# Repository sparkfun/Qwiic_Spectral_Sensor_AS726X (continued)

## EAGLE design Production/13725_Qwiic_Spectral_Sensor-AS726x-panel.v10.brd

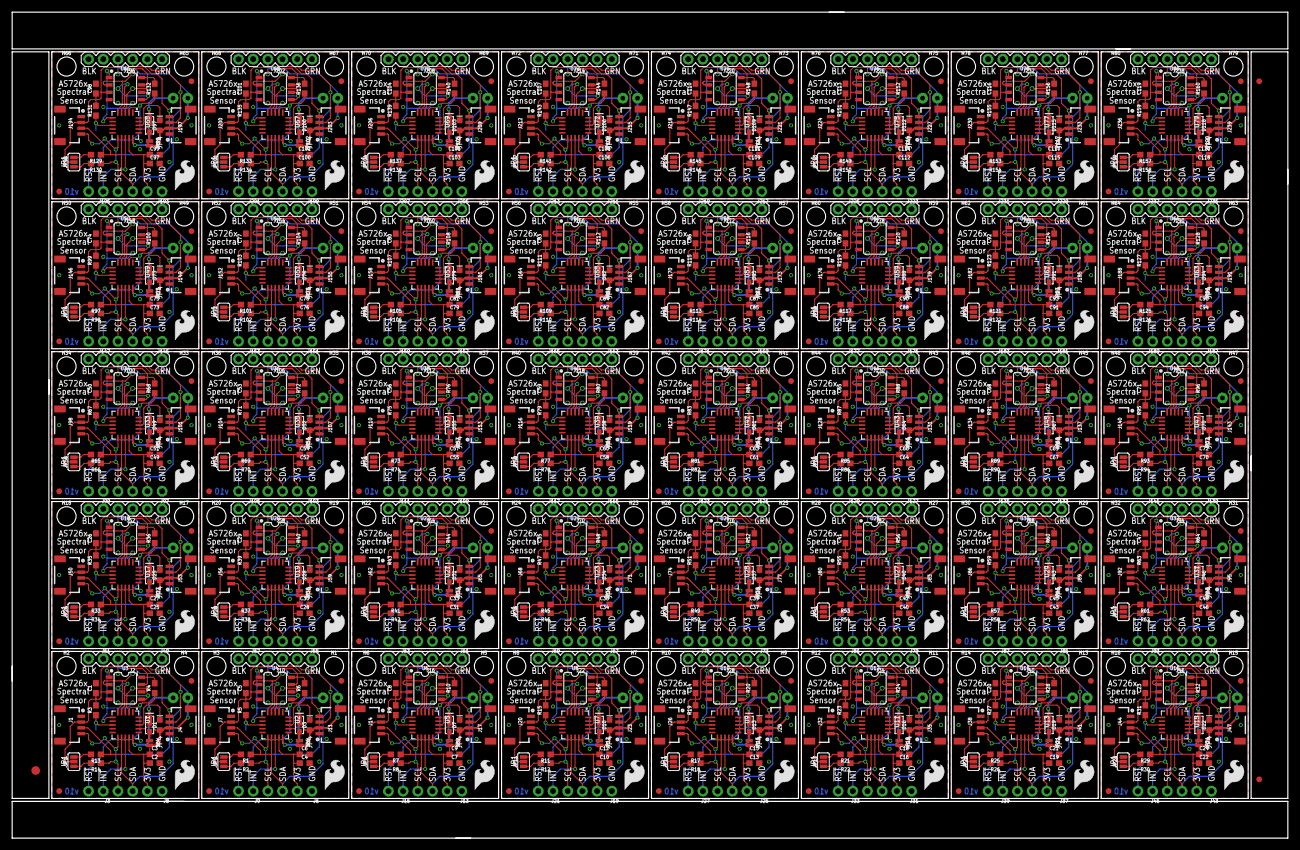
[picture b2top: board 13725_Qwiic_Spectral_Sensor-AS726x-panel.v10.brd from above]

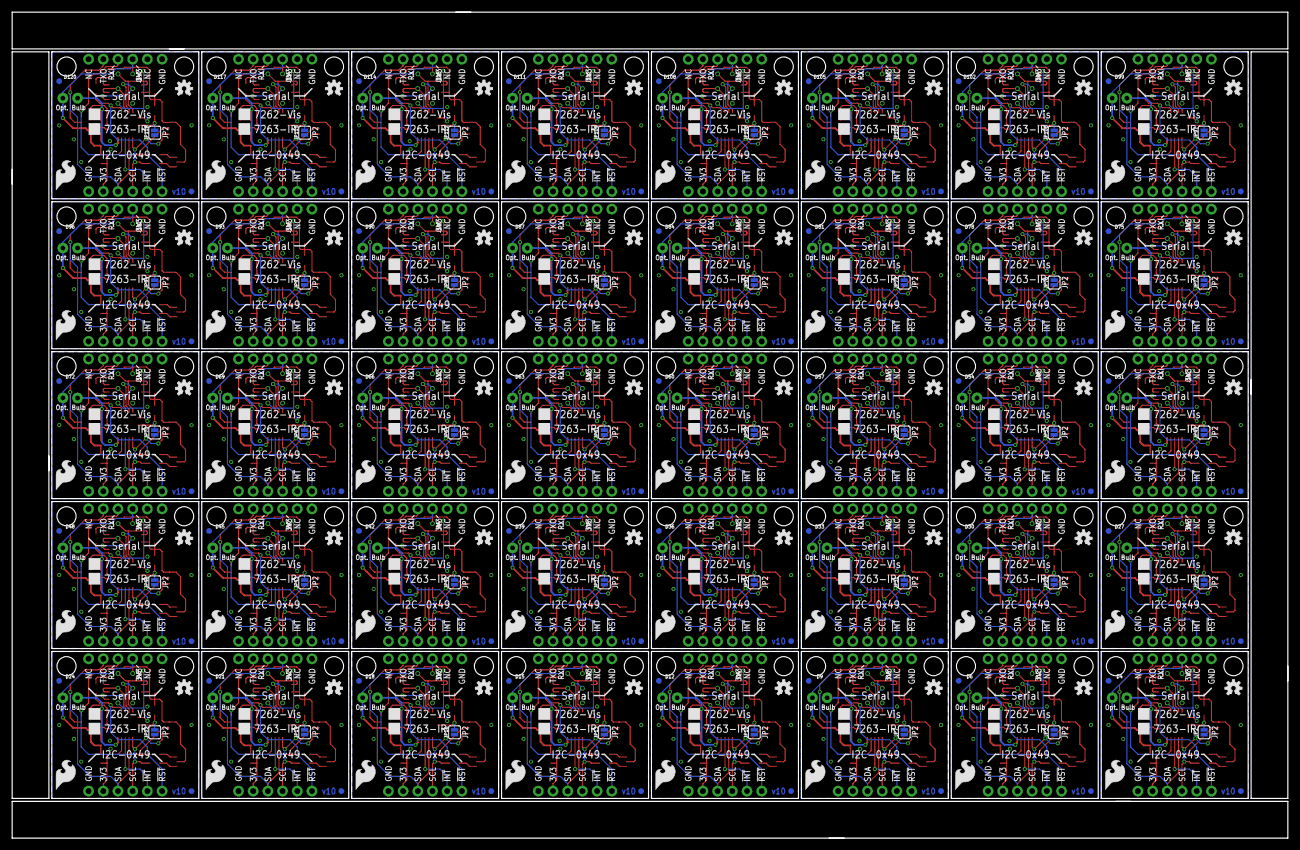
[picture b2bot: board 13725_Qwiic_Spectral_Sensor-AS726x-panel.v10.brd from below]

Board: 2 copper layers, 220.5 x 142.7 mm, 1203 parts (280 on the bottom side), 640 nets.

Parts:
C1, C2, C4, C5, C7, C8, C10, C11, C13, C14, C16, C17, C19, C20, C22, C23, C25, C26, C28, C29, C31, C32, C34, C35, C37, C38, C40, C41, C43, C44, C46, C47, C49, C50, C52, C53, C55, C56, C58, C59, C61, C62, C64, C65, C67, C68, C70, C71, C73, C74, C76, C77, C79, C80, C82, C83, C85, C86, C88, C89, C91, C92, C94, C95, C97, C98, C100, C101, C103, C104, C106, C107, C109, C110, C112, C113, C115, C116, C118, C119: 1.0uF; 0603
C3, C6, C9, C12, C15, C18, C21, C24, C27, C30, C33, C36, C39, C42, C45, C48, C51, C54, C57, C60, C63, C66, C69, C72, C75, C78, C81, C84, C87, C90, C93, C96, C99, C102, C105, C108, C111, C114, C117, C120: 10uF; 0603
D1, D3, D7, D10, D13, D16, D19, D22, D25, D28, D31, D34, D37, D40, D43, D46, D49, D52, D55, D58, D61, D64, D67, D70, D73, D76, D79, D82, D85, D88, D91, D94, D97, D100, D103, D106, D109, D112, D115, D118: BLUE; LED-0603
D2, D5, D8, D11, D14, D17, D20, D23, D26, D29, D32, D35, D38, D41, D44, D47, D50, D53, D56, D59, D62, D65, D68, D71, D74, D77, D80, D83, D86, D89, D92, D95, D98, D101, D104, D107, D110, D113, D116, D119: White, 60mA; SUPER_BRIGHT_SMD_LED_3014
D4, D6, D9, D12, D15, D18, D21, D24, D27, D30, D33, D36, D39, D42, D45, D48, D51, D54, D57, D60, D63, D66, D69, D72, D75, D78, D81, D84, D87, D90, D93, D96, D99, D102, D105, D108, D111, D114, D117, D120: Incandescent; LED_5MM_NOSILK
E$1: FIDUCIAL-1.5X3
E$7, E$8: FIDUCIAL-1X2
FD1, FD2, FD3, FD4, FD5, FD6, FD7, FD8, FD9, FD10, FD11, FD12, FD13, FD14, FD15, FD16, FD17, FD18, FD19, FD20, FD21, FD22, FD23, FD24, FD25, FD26, FD27, FD28, FD29, FD30, FD31, FD32, FD33, FD34, FD35, FD36, FD37, FD38, FD39, FD40, FD41, FD42, FD43, FD44, FD45, FD46, FD47, FD48, FD49, FD50, FD51, FD52, FD53, FD54, FD55, FD56, FD57, FD58, FD59, FD60, FD61, FD62, FD63, FD64, FD65, FD66, FD67, FD68, FD69, FD70, FD71, FD72, FD73, FD74, FD75, FD76, FD77, FD78, FD79, FD80, FD81, FD82, FD83, FD84, FD85, FD86, FD87, FD88, FD89, FD90, FD91, FD92, FD93, FD94, FD95, FD96, FD97, FD98, FD99, FD100, FD101, FD102, FD103, FD104, FD105, FD106, FD107, FD108, FD109, FD110, FD111, FD112, FD113, FD114, FD115, FD116, FD117, FD118, FD119, FD120, FD121, FD122, FD123, FD124, FD125, FD126, FD127, FD128, FD129, FD130, FD131, FD132, FD133, FD134, FD135, FD136, FD137, FD138, FD139, FD140, FD141, FD142, FD143, FD144, FD145, FD146, FD147, FD148, FD149, FD150, FD151, FD152, FD153, FD154, FD155, FD156, FD157, FD158, FD159, FD160: FIDUCIAL1X2; FIDUCIAL-1X2
H1, H2, H3, H4, H5, H6, H7, H8, H9, H10, H11, H12, H13, H14, H15, H16, H17, H18, H19, H20, H21, H22, H23, H24, H25, H26, H27, H28, H29, H30, H31, H32, H33, H34, H35, H36, H37, H38, H39, H40, H41, H42, H43, H44, H45, H46, H47, H48, H49, H50, H51, H52, H53, H54, H55, H56, H57, H58, H59, H60, H61, H62, H63, H64, H65, H66, H67, H68, H69, H70, H71, H72, H73, H74, H75, H76, H77, H78, H79, H80: STAND-OFF
J1, J4, J7, J11, J14, J17, J20, J23, J26, J29, J32, J35, J38, J41, J44, J47, J50, J53, J56, J59, J62, J65, J68, J71, J74, J77, J80, J83, J86, J89, J92, J95, J98, J101, J104, J107, J110, J113, J116, J119, J122, J125, J128, J131, J134, J137, J140, J143, J146, J149, J152, J155, J158, J161, J164, J167, J170, J173, J176, J179, J182, J185, J188, J191, J194, J197, J200, J203, J206, J209, J212, J215, J218, J221, J224, J227, J230, J233, J236, J239: Qwiic Right Angle; 1X04_1MM_RA
J2, J10, J16, J22, J28, J34, J40, J46, J52, J58, J64, J70, J76, J82, J88, J94, J100, J106, J112, J118, J124, J130, J136, J142, J148, J154, J160, J166, J172, J178, J184, J190, J196, J202, J208, J214, J220, J226, J232, J238: Serial Interface; FTDI_BASIC
J3, J9, J15, J21, J27, J33, J39, J45, J51, J57, J63, J69, J75, J81, J87, J93, J99, J105, J111, J117, J123, J129, J135, J141, J147, J153, J159, J165, J171, J177, J183, J189, J195, J201, J207, J213, J219, J225, J231, J237: 1X02_NO_SILK
J5, J12, J18, J24, J30, J36, J42, J48, J54, J60, J66, J72, J78, J84, J90, J96, J102, J108, J114, J120, J126, J132, J138, J144, J150, J156, J162, J168, J174, J180, J186, J192, J198, J204, J210, J216, J222, J228, J234, J240: Flash Programming; 2X3_TEST_POINTS
J6, J8, J13, J19, J25, J31, J37, J43, J49, J55, J61, J67, J73, J79, J85, J91, J97, J103, J109, J115, J121, J127, J133, J139, J145, J151, J157, J163, J169, J175, J181, J187, J193, J199, J205, J211, J217, J223, J229, J235: 1X04_NO_SILK
JP1, JP5, JP8, JP11, JP14, JP17, JP20, JP23, JP26, JP29, JP32, JP35, JP38, JP41, JP44, JP47, JP50, JP53, JP56, JP59, JP62, JP65, JP68, JP71, JP74, JP77, JP80, JP83, JP86, JP89, JP92, JP95, JP98, JP101, JP104, JP107, JP110, JP113, JP116, JP119: SMT-JUMPER_3_2-NC_PASTE_SILK
JP2, JP3, JP7, JP10, JP13, JP16, JP19, JP22, JP25, JP28, JP31, JP34, JP37, JP40, JP43, JP46, JP49, JP52, JP55, JP58, JP61, JP64, JP67, JP70, JP73, JP76, JP79, JP82, JP85, JP88, JP91, JP94, JP97, JP100, JP103, JP106, JP109, JP112, JP115, JP118: SMT-JUMPER_2_NO_SILK
JP4, JP6, JP9, JP12, JP15, JP18, JP21, JP24, JP27, JP30, JP33, JP36, JP39, JP42, JP45, JP48, JP51, JP54, JP57, JP60, JP63, JP66, JP69, JP72, JP75, JP78, JP81, JP84, JP87, JP90, JP93, JP96, JP99, JP102, JP105, JP108, JP111, JP114, JP117, JP120: SMT-JUMPER_2_NC_PASTE_NO-SILK
LOGO1, LOGO2, LOGO5, LOGO6, LOGO8, LOGO9, LOGO11, LOGO12, LOGO14, LOGO15, LOGO17, LOGO18, LOGO20, LOGO21, LOGO23, LOGO24, LOGO26, LOGO27, LOGO29, LOGO30, LOGO32, LOGO33, LOGO35, LOGO36, LOGO38, LOGO39, LOGO41, LOGO42, LOGO44, LOGO45, LOGO47, LOGO48, LOGO50, LOGO51, LOGO53, LOGO54, LOGO56, LOGO57, LOGO59, LOGO60, LOGO62, LOGO63, LOGO65, LOGO66, LOGO68, LOGO69, LOGO71, LOGO72, LOGO74, LOGO75, LOGO77, LOGO78, LOGO80, LOGO81, LOGO83, LOGO84, LOGO86, LOGO87, LOGO89, LOGO90, LOGO92, LOGO93, LOGO95, LOGO96, LOGO98, LOGO99, LOGO101, LOGO102, LOGO104, LOGO105, LOGO107, LOGO108, LOGO110, LOGO111, LOGO113, LOGO114, LOGO116, LOGO117, LOGO119, LOGO120: SFE_LOGO_FLAME.2_INCH; SFE_LOGO_FLAME_.2
LOGO3, LOGO4, LOGO7, LOGO10, LOGO13, LOGO16, LOGO19, LOGO22, LOGO25, LOGO28, LOGO31, LOGO34, LOGO37, LOGO40, LOGO43, LOGO46, LOGO49, LOGO52, LOGO55, LOGO58, LOGO61, LOGO64, LOGO67, LOGO70, LOGO73, LOGO76, LOGO79, LOGO82, LOGO85, LOGO88, LOGO91, LOGO94, LOGO97, LOGO100, LOGO103, LOGO106, LOGO109, LOGO112, LOGO115, LOGO118: OSHW-LOGOS; OSHW-LOGO-S
R1, R2, R7, R8, R11, R12, R13, R14, R17, R18, R21, R22, R25, R26, R29, R30, R33, R34, R37, R38, R41, R42, R45, R46, R49, R50, R53, R54, R57, R58, R61, R62, R65, R66, R69, R70, R73, R74, R77, R78, R81, R82, R85, R86, R89, R90, R93, R94, R97, R98, R101, R102, R105, R106, R109, R110, R113, R114, R117, R118, R121, R122, R125, R126, R129, R130, R133, R134, R137, R138, R141, R142, R145, R146, R149, R150, R153, R154, R157, R158: 4.7k; 0603
R3, R4, R5, R6, R9, R10, R15, R16, R19, R20, R23, R24, R27, R28, R31, R32, R35, R36, R39, R40, R43, R44, R47, R48, R51, R52, R55, R56, R59, R60, R63, R64, R67, R68, R71, R72, R75, R76, R79, R80, R83, R84, R87, R88, R91, R92, R95, R96, R99, R100, R103, R104, R107, R108, R111, R112, R115, R116, R119, R120, R123, R124, R127, R128, R131, R132, R135, R136, R139, R140, R143, R144, R147, R148, R151, R152, R155, R156, R159, R160: 10k; 0603
U1, U2, U5, U7, U9, U11, U13, U15, U17, U19, U21, U23, U25, U27, U29, U31, U33, U35, U37, U39, U41, U43, U45, U47, U49, U51, U53, U55, U57, U59, U61, U63, U65, U67, U69, U71, U73, U75, U77, U79: IR; LGA20
U3, U4, U6, U8, U10, U12, U14, U16, U18, U20, U22, U24, U26, U28, U30, U32, U34, U36, U38, U40, U42, U44, U46, U48, U50, U52, U54, U56, U58, U60, U62, U64, U66, U68, U70, U72, U74, U76, U78, U80: 4MB Flash; SO08

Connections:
3.3V: C1.1, C2.1, C3.1, D1.A, D4.A, J1.2, J2.VCC, J4.2, J5.2, J8.2, JP1.2, JP4.2, R3.2, R4.2, U1.14, U1.17, U3.3, U3.7, U3.8
3.3V1: C4.1, C5.1, C6.1, D3.A, D6.A, J6.2, J7.2, J10.VCC, J11.2, J12.2, JP5.2, JP6.2, R5.2, R6.2, U2.14, U2.17, U4.3, U4.7, U4.8
3.3V2: C7.1, C8.1, C9.1, D7.A, D9.A, J13.2, J14.2, J16.VCC, J17.2, J18.2, JP8.2, JP9.2, R9.2, R10.2, U5.14, U5.17, U6.3, U6.7, U6.8
3.3V3: C10.1, C11.1, C12.1, D10.A, D12.A, J19.2, J20.2, J22.VCC, J23.2, J24.2, JP11.2, JP12.2, R15.2, R16.2, U7.14, U7.17, U8.3, U8.7, U8.8
3.3V4: C13.1, C14.1, C15.1, D13.A, D15.A, J25.2, J26.2, J28.VCC, J29.2, J30.2, JP14.2, JP15.2, R19.2, R20.2, U9.14, U9.17, U10.3, U10.7, U10.8
3.3V5: C16.1, C17.1, C18.1, D16.A, D18.A, J31.2, J32.2, J34.VCC, J35.2, J36.2, JP17.2, JP18.2, R23.2, R24.2, U11.14, U11.17, U12.3, U12.7, U12.8
3.3V6: C19.1, C20.1, C21.1, D19.A, D21.A, J37.2, J38.2, J40.VCC, J41.2, J42.2, JP20.2, JP21.2, R27.2, R28.2, U13.14, U13.17, U14.3, U14.7, U14.8
3.3V7: C22.1, C23.1, C24.1, D22.A, D24.A, J43.2, J44.2, J46.VCC, J47.2, J48.2, JP23.2, JP24.2, R31.2, R32.2, U15.14, U15.17, U16.3, U16.7, U16.8
3.3V8: C25.1, C26.1, C27.1, D25.A, D27.A, J49.2, J50.2, J52.VCC, J53.2, J54.2, JP26.2, JP27.2, R35.2, R36.2, U17.14, U17.17, U18.3, U18.7, U18.8
3.3V9: C28.1, C29.1, C30.1, D28.A, D30.A, J55.2, J56.2, J58.VCC, J59.2, J60.2, JP29.2, JP30.2, R39.2, R40.2, U19.14, U19.17, U20.3, U20.7, U20.8
3.3V10: C31.1, C32.1, C33.1, D31.A, D33.A, J61.2, J62.2, J64.VCC, J65.2, J66.2, JP32.2, JP33.2, R43.2, R44.2, U21.14, U21.17, U22.3, U22.7, U22.8
3.3V11: C34.1, C35.1, C36.1, D34.A, D36.A, J67.2, J68.2, J70.VCC, J71.2, J72.2, JP35.2, JP36.2, R47.2, R48.2, U23.14, U23.17, U24.3, U24.7, U24.8
3.3V12: C37.1, C38.1, C39.1, D37.A, D39.A, J73.2, J74.2, J76.VCC, J77.2, J78.2, JP38.2, JP39.2, R51.2, R52.2, U25.14, U25.17, U26.3, U26.7, U26.8
3.3V13: C40.1, C41.1, C42.1, D40.A, D42.A, J79.2, J80.2, J82.VCC, J83.2, J84.2, JP41.2, JP42.2, R55.2, R56.2, U27.14, U27.17, U28.3, U28.7, U28.8
3.3V14: C43.1, C44.1, C45.1, D43.A, D45.A, J85.2, J86.2, J88.VCC, J89.2, J90.2, JP44.2, JP45.2, R59.2, R60.2, U29.14, U29.17, U30.3, U30.7, U30.8
3.3V15: C46.1, C47.1, C48.1, D46.A, D48.A, J91.2, J92.2, J94.VCC, J95.2, J96.2, JP47.2, JP48.2, R63.2, R64.2, U31.14, U31.17, U32.3, U32.7, U32.8
3.3V16: C49.1, C50.1, C51.1, D49.A, D51.A, J97.2, J98.2, J100.VCC, J101.2, J102.2, JP50.2, JP51.2, R67.2, R68.2, U33.14, U33.17, U34.3, U34.7, U34.8
3.3V17: C52.1, C53.1, C54.1, D52.A, D54.A, J103.2, J104.2, J106.VCC, J107.2, J108.2, JP53.2, JP54.2, R71.2, R72.2, U35.14, U35.17, U36.3, U36.7, U36.8
3.3V18: C55.1, C56.1, C57.1, D55.A, D57.A, J109.2, J110.2, J112.VCC, J113.2, J114.2, JP56.2, JP57.2, R75.2, R76.2, U37.14, U37.17, U38.3, U38.7, U38.8
3.3V19: C58.1, C59.1, C60.1, D58.A, D60.A, J115.2, J116.2, J118.VCC, J119.2, J120.2, JP59.2, JP60.2, R79.2, R80.2, U39.14, U39.17, U40.3, U40.7, U40.8
3.3V20: C61.1, C62.1, C63.1, D61.A, D63.A, J121.2, J122.2, J124.VCC, J125.2, J126.2, JP62.2, JP63.2, R83.2, R84.2, U41.14, U41.17, U42.3, U42.7, U42.8
3.3V21: C64.1, C65.1, C66.1, D64.A, D66.A, J127.2, J128.2, J130.VCC, J131.2, J132.2, JP65.2, JP66.2, R87.2, R88.2, U43.14, U43.17, U44.3, U44.7, U44.8
3.3V22: C67.1, C68.1, C69.1, D67.A, D69.A, J133.2, J134.2, J136.VCC, J137.2, J138.2, JP68.2, JP69.2, R91.2, R92.2, U45.14, U45.17, U46.3, U46.7, U46.8
3.3V23: C70.1, C71.1, C72.1, D70.A, D72.A, J139.2, J140.2, J142.VCC, J143.2, J144.2, JP71.2, JP72.2, R95.2, R96.2, U47.14, U47.17, U48.3, U48.7, U48.8
3.3V24: C73.1, C74.1, C75.1, D73.A, D75.A, J145.2, J146.2, J148.VCC, J149.2, J150.2, JP74.2, JP75.2, R99.2, R100.2, U49.14, U49.17, U50.3, U50.7, U50.8
3.3V25: C76.1, C77.1, C78.1, D76.A, D78.A, J151.2, J152.2, J154.VCC, J155.2, J156.2, JP77.2, JP78.2, R103.2, R104.2, U51.14, U51.17, U52.3, U52.7, U52.8
3.3V26: C79.1, C80.1, C81.1, D79.A, D81.A, J157.2, J158.2, J160.VCC, J161.2, J162.2, JP80.2, JP81.2, R107.2, R108.2, U53.14, U53.17, U54.3, U54.7, U54.8
3.3V27: C82.1, C83.1, C84.1, D82.A, D84.A, J163.2, J164.2, J166.VCC, J167.2, J168.2, JP83.2, JP84.2, R111.2, R112.2, U55.14, U55.17, U56.3, U56.7, U56.8
3.3V28: C85.1, C86.1, C87.1, D85.A, D87.A, J169.2, J170.2, J172.VCC, J173.2, J174.2, JP86.2, JP87.2, R115.2, R116.2, U57.14, U57.17, U58.3, U58.7, U58.8
3.3V29: C88.1, C89.1, C90.1, D88.A, D90.A, J175.2, J176.2, J178.VCC, J179.2, J180.2, JP89.2, JP90.2, R119.2, R120.2, U59.14, U59.17, U60.3, U60.7, U60.8
3.3V30: C91.1, C92.1, C93.1, D91.A, D93.A, J181.2, J182.2, J184.VCC, J185.2, J186.2, JP92.2, JP93.2, R123.2, R124.2, U61.14, U61.17, U62.3, U62.7, U62.8
3.3V31: C94.1, C95.1, C96.1, D94.A, D96.A, J187.2, J188.2, J190.VCC, J191.2, J192.2, JP95.2, JP96.2, R127.2, R128.2, U63.14, U63.17, U64.3, U64.7, U64.8
3.3V32: C97.1, C98.1, C99.1, D97.A, D99.A, J193.2, J194.2, J196.VCC, J197.2, J198.2, JP98.2, JP99.2, R131.2, R132.2, U65.14, U65.17, U66.3, U66.7, U66.8
3.3V33: C100.1, C101.1, C102.1, D100.A, D102.A, J199.2, J200.2, J202.VCC, J203.2, J204.2, JP101.2, JP102.2, R135.2, R136.2, U67.14, U67.17, U68.3, U68.7, U68.8
3.3V34: C103.1, C104.1, C105.1, D103.A, D105.A, J205.2, J206.2, J208.VCC, J209.2, J210.2, JP104.2, JP105.2, R139.2, R140.2, U69.14, U69.17, U70.3, U70.7, U70.8
3.3V35: C106.1, C107.1, C108.1, D106.A, D108.A, J211.2, J212.2, J214.VCC, J215.2, J216.2, JP107.2, JP108.2, R143.2, R144.2, U71.14, U71.17, U72.3, U72.7, U72.8
3.3V36: C109.1, C110.1, C111.1, D109.A, D111.A, J217.2, J218.2, J220.VCC, J221.2, J222.2, JP110.2, JP111.2, R147.2, R148.2, U73.14, U73.17, U74.3, U74.7, U74.8
3.3V37: C112.1, C113.1, C114.1, D112.A, D114.A, J223.2, J224.2, J226.VCC, J227.2, J228.2, JP113.2, JP114.2, R151.2, R152.2, U75.14, U75.17, U76.3, U76.7, U76.8
3.3V38: C115.1, C116.1, C117.1, D115.A, D117.A, J229.2, J230.2, J232.VCC, J233.2, J234.2, JP116.2, JP117.2, R155.2, R156.2, U77.14, U77.17, U78.3, U78.7, U78.8
3.3V39: C118.1, C119.1, C120.1, D118.A, D120.A, J235.2, J236.2, J238.VCC, J239.2, J240.2, JP119.2, JP120.2, R159.2, R160.2, U79.14, U79.17, U80.3, U80.7, U80.8
!CS_EE: J5.5, U1.6, U3.1
!CS_EE1: J12.5, U2.6, U4.1
!CS_EE2: J18.5, U5.6, U6.1
!CS_EE3: J24.5, U7.6, U8.1
!CS_EE4: J30.5, U9.6, U10.1
!CS_EE5: J36.5, U11.6, U12.1
!CS_EE6: J42.5, U13.6, U14.1
!CS_EE7: J48.5, U15.6, U16.1
!CS_EE8: J54.5, U17.6, U18.1
!CS_EE9: J60.5, U19.6, U20.1
!CS_EE10: J66.5, U21.6, U22.1
!CS_EE11: J72.5, U23.6, U24.1
!CS_EE12: J78.5, U25.6, U26.1
!CS_EE13: J84.5, U27.6, U28.1
!CS_EE14: J90.5, U29.6, U30.1
!CS_EE15: J96.5, U31.6, U32.1
!CS_EE16: J102.5, U33.6, U34.1
!CS_EE17: J108.5, U35.6, U36.1
!CS_EE18: J114.5, U37.6, U38.1
!CS_EE19: J120.5, U39.6, U40.1
!CS_EE20: J126.5, U41.6, U42.1
!CS_EE21: J132.5, U43.6, U44.1
!CS_EE22: J138.5, U45.6, U46.1
!CS_EE23: J144.5, U47.6, U48.1
!CS_EE24: J150.5, U49.6, U50.1
!CS_EE25: J156.5, U51.6, U52.1
!CS_EE26: J162.5, U53.6, U54.1
!CS_EE27: J168.5, U55.6, U56.1
!CS_EE28: J174.5, U57.6, U58.1
!CS_EE29: J180.5, U59.6, U60.1
!CS_EE30: J186.5, U61.6, U62.1
!CS_EE31: J192.5, U63.6, U64.1
!CS_EE32: J198.5, U65.6, U66.1
!CS_EE33: J204.5, U67.6, U68.1
!CS_EE34: J210.5, U69.6, U70.1
!CS_EE35: J216.5, U71.6, U72.1
!CS_EE36: J222.5, U73.6, U74.1
!CS_EE37: J228.5, U75.6, U76.1
!CS_EE38: J234.5, U77.6, U78.1
!CS_EE39: J240.5, U79.6, U80.1
!INT: J3.1, U1.13
!INT1: J9.1, U2.13
!INT2: J15.1, U5.13
!INT3: J21.1, U7.13
!INT4: J27.1, U9.13
!INT5: J33.1, U11.13
!INT6: J39.1, U13.13
!INT7: J45.1, U15.13
!INT8: J51.1, U17.13
!INT9: J57.1, U19.13
!INT10: J63.1, U21.13
!INT11: J69.1, U23.13
!INT12: J75.1, U25.13
!INT13: J81.1, U27.13
!INT14: J87.1, U29.13
!INT15: J93.1, U31.13
!INT16: J99.1, U33.13
!INT17: J105.1, U35.13
!INT18: J111.1, U37.13
!INT19: J117.1, U39.13
!INT20: J123.1, U41.13
!INT21: J129.1, U43.13
!INT22: J135.1, U45.13
!INT23: J141.1, U47.13
!INT24: J147.1, U49.13
!INT25: J153.1, U51.13
!INT26: J159.1, U53.13
!INT27: J165.1, U55.13
!INT28: J171.1, U57.13
!INT29: J177.1, U59.13
!INT30: J183.1, U61.13
!INT31: J189.1, U63.13
!INT32: J195.1, U65.13
!INT33: J201.1, U67.13
!INT34: J207.1, U69.13
!INT35: J213.1, U71.13
!INT36: J219.1, U73.13
!INT37: J225.1, U75.13
!INT38: J231.1, U77.13
!INT39: J237.1, U79.13
!RST: J3.2, R4.1, U1.2
!RST1: J9.2, R6.1, U2.2
!RST2: J15.2, R10.1, U5.2
!RST3: J21.2, R16.1, U7.2
!RST4: J27.2, R20.1, U9.2
!RST5: J33.2, R24.1, U11.2
!RST6: J39.2, R28.1, U13.2
!RST7: J45.2, R32.1, U15.2
!RST8: J51.2, R36.1, U17.2
!RST9: J57.2, R40.1, U19.2
!RST10: J63.2, R44.1, U21.2
!RST11: J69.2, R48.1, U23.2
!RST12: J75.2, R52.1, U25.2
!RST13: J81.2, R56.1, U27.2
!RST14: J87.2, R60.1, U29.2
!RST15: J93.2, R64.1, U31.2
!RST16: J99.2, R68.1, U33.2
!RST17: J105.2, R72.1, U35.2
!RST18: J111.2, R76.1, U37.2
!RST19: J117.2, R80.1, U39.2
!RST20: J123.2, R84.1, U41.2
!RST21: J129.2, R88.1, U43.2
!RST22: J135.2, R92.1, U45.2
!RST23: J141.2, R96.1, U47.2
!RST24: J147.2, R100.1, U49.2
!RST25: J153.2, R104.1, U51.2
!RST26: J159.2, R108.1, U53.2
!RST27: J165.2, R112.1, U55.2
!RST28: J171.2, R116.1, U57.2
!RST29: J177.2, R120.1, U59.2
!RST30: J183.2, R124.1, U61.2
!RST31: J189.2, R128.1, U63.2
!RST32: J195.2, R132.1, U65.2
!RST33: J201.2, R136.1, U67.2
!RST34: J207.2, R140.1, U69.2
!RST35: J213.2, R144.1, U71.2
!RST36: J219.2, R148.1, U73.2
!RST37: J225.2, R152.1, U75.2
!RST38: J231.2, R156.1, U77.2
!RST39: J237.2, R160.1, U79.2
GND: C1.2, C2.2, C3.2, J1.1, J2.GND, J4.1, J5.6, J8.1, JP2.1, U1.16, U3.4
GND1: C4.2, C5.2, C6.2, J6.1, J7.1, J10.GND, J11.1, J12.6, JP3.1, U2.16, U4.4
GND2: C7.2, C8.2, C9.2, J13.1, J14.1, J16.GND, J17.1, J18.6, JP7.1, U5.16, U6.4
GND3: C10.2, C11.2, C12.2, J19.1, J20.1, J22.GND, J23.1, J24.6, JP10.1, U7.16, U8.4
GND4: C13.2, C14.2, C15.2, J25.1, J26.1, J28.GND, J29.1, J30.6, JP13.1, U9.16, U10.4
GND5: C16.2, C17.2, C18.2, J31.1, J32.1, J34.GND, J35.1, J36.6, JP16.1, U11.16, U12.4
GND6: C19.2, C20.2, C21.2, J37.1, J38.1, J40.GND, J41.1, J42.6, JP19.1, U13.16, U14.4
GND7: C22.2, C23.2, C24.2, J43.1, J44.1, J46.GND, J47.1, J48.6, JP22.1, U15.16, U16.4
GND8: C25.2, C26.2, C27.2, J49.1, J50.1, J52.GND, J53.1, J54.6, JP25.1, U17.16, U18.4
GND9: C28.2, C29.2, C30.2, J55.1, J56.1, J58.GND, J59.1, J60.6, JP28.1, U19.16, U20.4
GND10: C31.2, C32.2, C33.2, J61.1, J62.1, J64.GND, J65.1, J66.6, JP31.1, U21.16, U22.4
GND11: C34.2, C35.2, C36.2, J67.1, J68.1, J70.GND, J71.1, J72.6, JP34.1, U23.16, U24.4
GND12: C37.2, C38.2, C39.2, J73.1, J74.1, J76.GND, J77.1, J78.6, JP37.1, U25.16, U26.4
GND13: C40.2, C41.2, C42.2, J79.1, J80.1, J82.GND, J83.1, J84.6, JP40.1, U27.16, U28.4
GND14: C43.2, C44.2, C45.2, J85.1, J86.1, J88.GND, J89.1, J90.6, JP43.1, U29.16, U30.4
GND15: C46.2, C47.2, C48.2, J91.1, J92.1, J94.GND, J95.1, J96.6, JP46.1, U31.16, U32.4
GND16: C49.2, C50.2, C51.2, J97.1, J98.1, J100.GND, J101.1, J102.6, JP49.1, U33.16, U34.4
GND17: C52.2, C53.2, C54.2, J103.1, J104.1, J106.GND, J107.1, J108.6, JP52.1, U35.16, U36.4
GND18: C55.2, C56.2, C57.2, J109.1, J110.1, J112.GND, J113.1, J114.6, JP55.1, U37.16, U38.4
GND19: C58.2, C59.2, C60.2, J115.1, J116.1, J118.GND, J119.1, J120.6, JP58.1, U39.16, U40.4
GND20: C61.2, C62.2, C63.2, J121.1, J122.1, J124.GND, J125.1, J126.6, JP61.1, U41.16, U42.4
GND21: C64.2, C65.2, C66.2, J127.1, J128.1, J130.GND, J131.1, J132.6, JP64.1, U43.16, U44.4
GND22: C67.2, C68.2, C69.2, J133.1, J134.1, J136.GND, J137.1, J138.6, JP67.1, U45.16, U46.4
GND23: C70.2, C71.2, C72.2, J139.1, J140.1, J142.GND, J143.1, J144.6, JP70.1, U47.16, U48.4
GND24: C73.2, C74.2, C75.2, J145.1, J146.1, J148.GND, J149.1, J150.6, JP73.1, U49.16, U50.4
GND25: C76.2, C77.2, C78.2, J151.1, J152.1, J154.GND, J155.1, J156.6, JP76.1, U51.16, U52.4
GND26: C79.2, C80.2, C81.2, J157.1, J158.1, J160.GND, J161.1, J162.6, JP79.1, U53.16, U54.4
GND27: C82.2, C83.2, C84.2, J163.1, J164.1, J166.GND, J167.1, J168.6, JP82.1, U55.16, U56.4
GND28: C85.2, C86.2, C87.2, J169.1, J170.1, J172.GND, J173.1, J174.6, JP85.1, U57.16, U58.4
GND29: C88.2, C89.2, C90.2, J175.1, J176.1, J178.GND, J179.1, J180.6, JP88.1, U59.16, U60.4
GND30: C91.2, C92.2, C93.2, J181.1, J182.1, J184.GND, J185.1, J186.6, JP91.1, U61.16, U62.4
GND31: C94.2, C95.2, C96.2, J187.1, J188.1, J190.GND, J191.1, J192.6, JP94.1, U63.16, U64.4
GND32: C97.2, C98.2, C99.2, J193.1, J194.1, J196.GND, J197.1, J198.6, JP97.1, U65.16, U66.4
GND33: C100.2, C101.2, C102.2, J199.1, J200.1, J202.GND, J203.1, J204.6, JP100.1, U67.16, U68.4
GND34: C103.2, C104.2, C105.2, J205.1, J206.1, J208.GND, J209.1, J210.6, JP103.1, U69.16, U70.4
GND35: C106.2, C107.2, C108.2, J211.1, J212.1, J214.GND, J215.1, J216.6, JP106.1, U71.16, U72.4
GND36: C109.2, C110.2, C111.2, J217.1, J218.1, J220.GND, J221.1, J222.6, JP109.1, U73.16, U74.4
GND37: C112.2, C113.2, C114.2, J223.1, J224.1, J226.GND, J227.1, J228.6, JP112.1, U75.16, U76.4
GND38: C115.2, C116.2, C117.2, J229.1, J230.1, J232.GND, J233.1, J234.6, JP115.1, U77.16, U78.4
GND39: C118.2, C119.2, C120.2, J235.1, J236.1, J238.GND, J239.1, J240.6, JP118.1, U79.16, U80.4
LED_DRV: D2.C, D4.K, U1.15
LED_DRV1: D5.C, D6.K, U2.15
LED_DRV2: D8.C, D9.K, U5.15
LED_DRV3: D11.C, D12.K, U7.15
LED_DRV4: D14.C, D15.K, U9.15
LED_DRV5: D17.C, D18.K, U11.15
LED_DRV6: D20.C, D21.K, U13.15
LED_DRV7: D23.C, D24.K, U15.15
LED_DRV8: D26.C, D27.K, U17.15
LED_DRV9: D29.C, D30.K, U19.15
LED_DRV10: D32.C, D33.K, U21.15
LED_DRV11: D35.C, D36.K, U23.15
LED_DRV12: D38.C, D39.K, U25.15
LED_DRV13: D41.C, D42.K, U27.15
LED_DRV14: D44.C, D45.K, U29.15
LED_DRV15: D47.C, D48.K, U31.15
LED_DRV16: D50.C, D51.K, U33.15
LED_DRV17: D53.C, D54.K, U35.15
LED_DRV18: D56.C, D57.K, U37.15
LED_DRV19: D59.C, D60.K, U39.15
LED_DRV20: D62.C, D63.K, U41.15
LED_DRV21: D65.C, D66.K, U43.15
LED_DRV22: D68.C, D69.K, U45.15
LED_DRV23: D71.C, D72.K, U47.15
LED_DRV24: D74.C, D75.K, U49.15
LED_DRV25: D77.C, D78.K, U51.15
LED_DRV26: D80.C, D81.K, U53.15
LED_DRV27: D83.C, D84.K, U55.15
LED_DRV28: D86.C, D87.K, U57.15
LED_DRV29: D89.C, D90.K, U59.15
LED_DRV30: D92.C, D93.K, U61.15
LED_DRV31: D95.C, D96.K, U63.15
LED_DRV32: D98.C, D99.K, U65.15
LED_DRV33: D101.C, D102.K, U67.15
LED_DRV34: D104.C, D105.K, U69.15
LED_DRV35: D107.C, D108.K, U71.15
LED_DRV36: D110.C, D111.K, U73.15
LED_DRV37: D113.C, D114.K, U75.15
LED_DRV38: D116.C, D117.K, U77.15
LED_DRV39: D119.C, D120.K, U79.15
MISO: J5.1, U1.5, U3.2
MISO1: J12.1, U2.5, U4.2
MISO2: J18.1, U5.5, U6.2
MISO3: J24.1, U7.5, U8.2
MISO4: J30.1, U9.5, U10.2
MISO5: J36.1, U11.5, U12.2
MISO6: J42.1, U13.5, U14.2
MISO7: J48.1, U15.5, U16.2
MISO8: J54.1, U17.5, U18.2
MISO9: J60.1, U19.5, U20.2
MISO10: J66.1, U21.5, U22.2
MISO11: J72.1, U23.5, U24.2
MISO12: J78.1, U25.5, U26.2
MISO13: J84.1, U27.5, U28.2
MISO14: J90.1, U29.5, U30.2
MISO15: J96.1, U31.5, U32.2
MISO16: J102.1, U33.5, U34.2
MISO17: J108.1, U35.5, U36.2
MISO18: J114.1, U37.5, U38.2
MISO19: J120.1, U39.5, U40.2
MISO20: J126.1, U41.5, U42.2
MISO21: J132.1, U43.5, U44.2
MISO22: J138.1, U45.5, U46.2
MISO23: J144.1, U47.5, U48.2
MISO24: J150.1, U49.5, U50.2
MISO25: J156.1, U51.5, U52.2
MISO26: J162.1, U53.5, U54.2
MISO27: J168.1, U55.5, U56.2
MISO28: J174.1, U57.5, U58.2
MISO29: J180.1, U59.5, U60.2
MISO30: J186.1, U61.5, U62.2
MISO31: J192.1, U63.5, U64.2
MISO32: J198.1, U65.5, U66.2
MISO33: J204.1, U67.5, U68.2
MISO34: J210.1, U69.5, U70.2
MISO35: J216.1, U71.5, U72.2
MISO36: J222.1, U73.5, U74.2
MISO37: J228.1, U75.5, U76.2
MISO38: J234.1, U77.5, U78.2
MISO39: J240.1, U79.5, U80.2
MOSI: J5.4, U1.4, U3.5
MOSI1: J12.4, U2.4, U4.5
MOSI2: J18.4, U5.4, U6.5
MOSI3: J24.4, U7.4, U8.5
MOSI4: J30.4, U9.4, U10.5
MOSI5: J36.4, U11.4, U12.5
MOSI6: J42.4, U13.4, U14.5
MOSI7: J48.4, U15.4, U16.5
MOSI8: J54.4, U17.4, U18.5
MOSI9: J60.4, U19.4, U20.5
MOSI10: J66.4, U21.4, U22.5
MOSI11: J72.4, U23.4, U24.5
MOSI12: J78.4, U25.4, U26.5
MOSI13: J84.4, U27.4, U28.5
MOSI14: J90.4, U29.4, U30.5
MOSI15: J96.4, U31.4, U32.5
MOSI16: J102.4, U33.4, U34.5
MOSI17: J108.4, U35.4, U36.5
MOSI18: J114.4, U37.4, U38.5
MOSI19: J120.4, U39.4, U40.5
MOSI20: J126.4, U41.4, U42.5
MOSI21: J132.4, U43.4, U44.5
MOSI22: J138.4, U45.4, U46.5
MOSI23: J144.4, U47.4, U48.5
MOSI24: J150.4, U49.4, U50.5
MOSI25: J156.4, U51.4, U52.5
MOSI26: J162.4, U53.4, U54.5
MOSI27: J168.4, U55.4, U56.5
MOSI28: J174.4, U57.4, U58.5
MOSI29: J180.4, U59.4, U60.5
MOSI30: J186.4, U61.4, U62.5
MOSI31: J192.4, U63.4, U64.5
MOSI32: J198.4, U65.4, U66.5
MOSI33: J204.4, U67.4, U68.5
MOSI34: J210.4, U69.4, U70.5
MOSI35: J216.4, U71.4, U72.5
MOSI36: J222.4, U73.4, U74.5
MOSI37: J228.4, U75.4, U76.5
MOSI38: J234.4, U77.4, U78.5
MOSI39: J240.4, U79.4, U80.5
unnamed: JP2.2, R3.1, U1.8
unnamed: D1.C, U1.18
unnamed: JP5.3, R1.2
unnamed: JP1.3, R13.2
unnamed: JP1.1, R14.2
unnamed: D2.A, JP4.1
unnamed: JP5.1, R2.2
unnamed: JP3.2, R5.1, U2.8
unnamed: D3.C, U2.18
unnamed: D5.A, JP6.1
unnamed: JP8.3, R7.2
unnamed: JP8.1, R8.2
unnamed: JP7.2, R9.1, U5.8
unnamed: D7.C, U5.18
unnamed: D8.A, JP9.1
unnamed: JP11.3, R11.2
unnamed: JP11.1, R12.2
unnamed: JP10.2, R15.1, U7.8
unnamed: D10.C, U7.18
unnamed: D11.A, JP12.1
unnamed: JP14.3, R17.2
unnamed: JP14.1, R18.2
unnamed: JP13.2, R19.1, U9.8
unnamed: D13.C, U9.18
unnamed: D14.A, JP15.1
unnamed: JP17.3, R21.2
unnamed: JP17.1, R22.2
unnamed: JP16.2, R23.1, U11.8
unnamed: D16.C, U11.18
unnamed: D17.A, JP18.1
unnamed: JP20.3, R25.2
unnamed: JP20.1, R26.2
unnamed: JP19.2, R27.1, U13.8
unnamed: D19.C, U13.18
unnamed: D20.A, JP21.1
unnamed: JP23.3, R29.2
unnamed: JP23.1, R30.2
unnamed: JP22.2, R31.1, U15.8
unnamed: D22.C, U15.18
unnamed: D23.A, JP24.1
unnamed: JP26.3, R33.2
unnamed: JP26.1, R34.2
unnamed: JP25.2, R35.1, U17.8
unnamed: D25.C, U17.18
unnamed: D26.A, JP27.1
unnamed: JP29.3, R37.2
unnamed: JP29.1, R38.2
unnamed: JP28.2, R39.1, U19.8
unnamed: D28.C, U19.18
unnamed: D29.A, JP30.1
unnamed: JP32.3, R41.2
unnamed: JP32.1, R42.2
unnamed: JP31.2, R43.1, U21.8
unnamed: D31.C, U21.18
unnamed: D32.A, JP33.1
unnamed: JP35.3, R45.2
unnamed: JP35.1, R46.2
unnamed: JP34.2, R47.1, U23.8
unnamed: D34.C, U23.18
unnamed: D35.A, JP36.1
unnamed: JP38.3, R49.2
unnamed: JP38.1, R50.2
unnamed: JP37.2, R51.1, U25.8
unnamed: D37.C, U25.18
unnamed: D38.A, JP39.1
unnamed: JP41.3, R53.2
unnamed: JP41.1, R54.2
unnamed: JP40.2, R55.1, U27.8
unnamed: D40.C, U27.18
unnamed: D41.A, JP42.1
unnamed: JP44.3, R57.2
unnamed: JP44.1, R58.2
unnamed: JP43.2, R59.1, U29.8
unnamed: D43.C, U29.18
unnamed: D44.A, JP45.1
unnamed: JP47.3, R61.2
unnamed: JP47.1, R62.2
unnamed: JP46.2, R63.1, U31.8
unnamed: D46.C, U31.18
unnamed: D47.A, JP48.1
unnamed: JP50.3, R65.2
unnamed: JP50.1, R66.2
unnamed: JP49.2, R67.1, U33.8
unnamed: D49.C, U33.18
unnamed: D50.A, JP51.1
unnamed: JP53.3, R69.2
unnamed: JP53.1, R70.2
unnamed: JP52.2, R71.1, U35.8
unnamed: D52.C, U35.18
unnamed: D53.A, JP54.1
unnamed: JP56.3, R73.2
unnamed: JP56.1, R74.2
unnamed: JP55.2, R75.1, U37.8
unnamed: D55.C, U37.18
unnamed: D56.A, JP57.1
unnamed: JP59.3, R77.2
unnamed: JP59.1, R78.2
unnamed: JP58.2, R79.1, U39.8
unnamed: D58.C, U39.18
unnamed: D59.A, JP60.1
unnamed: JP62.3, R81.2
unnamed: JP62.1, R82.2
unnamed: JP61.2, R83.1, U41.8
unnamed: D61.C, U41.18
unnamed: D62.A, JP63.1
unnamed: JP65.3, R85.2
unnamed: JP65.1, R86.2
unnamed: JP64.2, R87.1, U43.8
unnamed: D64.C, U43.18
unnamed: D65.A, JP66.1
unnamed: JP68.3, R89.2
unnamed: JP68.1, R90.2
unnamed: JP67.2, R91.1, U45.8
unnamed: D67.C, U45.18
unnamed: D68.A, JP69.1
unnamed: JP71.3, R93.2
unnamed: JP71.1, R94.2
unnamed: JP70.2, R95.1, U47.8
unnamed: D70.C, U47.18
unnamed: D71.A, JP72.1
unnamed: JP74.3, R97.2
unnamed: JP74.1, R98.2
unnamed: JP73.2, R99.1, U49.8
unnamed: D73.C, U49.18
unnamed: D74.A, JP75.1
unnamed: JP77.3, R101.2
unnamed: JP77.1, R102.2
unnamed: JP76.2, R103.1, U51.8
unnamed: D76.C, U51.18
unnamed: D77.A, JP78.1
unnamed: JP80.3, R105.2
unnamed: JP80.1, R106.2
unnamed: JP79.2, R107.1, U53.8
unnamed: D79.C, U53.18
unnamed: D80.A, JP81.1
unnamed: JP83.3, R109.2
unnamed: JP83.1, R110.2
unnamed: JP82.2, R111.1, U55.8
unnamed: D82.C, U55.18
unnamed: D83.A, JP84.1
unnamed: JP86.3, R113.2
unnamed: JP86.1, R114.2
unnamed: JP85.2, R115.1, U57.8
unnamed: D85.C, U57.18
unnamed: D86.A, JP87.1
unnamed: JP89.3, R117.2
unnamed: JP89.1, R118.2
unnamed: JP88.2, R119.1, U59.8
unnamed: D88.C, U59.18
unnamed: D89.A, JP90.1
unnamed: JP92.3, R121.2
unnamed: JP92.1, R122.2
unnamed: JP91.2, R123.1, U61.8
unnamed: D91.C, U61.18
unnamed: D92.A, JP93.1
unnamed: JP95.3, R125.2
unnamed: JP95.1, R126.2
unnamed: JP94.2, R127.1, U63.8
unnamed: D94.C, U63.18
unnamed: D95.A, JP96.1
unnamed: JP98.3, R129.2
unnamed: JP98.1, R130.2
unnamed: JP97.2, R131.1, U65.8
unnamed: D97.C, U65.18
unnamed: D98.A, JP99.1
unnamed: JP101.3, R133.2
unnamed: JP101.1, R134.2
unnamed: JP100.2, R135.1, U67.8
unnamed: D100.C, U67.18
unnamed: D101.A, JP102.1
unnamed: JP104.3, R137.2
unnamed: JP104.1, R138.2
unnamed: JP103.2, R139.1, U69.8
unnamed: D103.C, U69.18
unnamed: D104.A, JP105.1
unnamed: JP107.3, R141.2
unnamed: JP107.1, R142.2
unnamed: JP106.2, R143.1, U71.8
unnamed: D106.C, U71.18
unnamed: D107.A, JP108.1
unnamed: JP110.3, R145.2
unnamed: JP110.1, R146.2
unnamed: JP109.2, R147.1, U73.8
unnamed: D109.C, U73.18
unnamed: D110.A, JP111.1
unnamed: JP113.3, R149.2
unnamed: JP113.1, R150.2
unnamed: JP112.2, R151.1, U75.8
unnamed: D112.C, U75.18
unnamed: D113.A, JP114.1
unnamed: JP116.3, R153.2
unnamed: JP116.1, R154.2
unnamed: JP115.2, R155.1, U77.8
unnamed: D115.C, U77.18
unnamed: D116.A, JP117.1
unnamed: JP119.3, R157.2
unnamed: JP119.1, R158.2
unnamed: JP118.2, R159.1, U79.8
unnamed: D118.C, U79.18
unnamed: D119.A, JP120.1
RX/SCL: J1.4, J2.TXO, J4.4, J8.4, R14.1, U1.11
RX/SCL1: J6.4, J7.4, J10.TXO, J11.4, R2.1, U2.11
RX/SCL2: J13.4, J14.4, J16.TXO, J17.4, R8.1, U5.11
RX/SCL3: J19.4, J20.4, J22.TXO, J23.4, R12.1, U7.11
RX/SCL4: J25.4, J26.4, J28.TXO, J29.4, R18.1, U9.11
RX/SCL5: J31.4, J32.4, J34.TXO, J35.4, R22.1, U11.11
RX/SCL6: J37.4, J38.4, J40.TXO, J41.4, R26.1, U13.11
RX/SCL7: J43.4, J44.4, J46.TXO, J47.4, R30.1, U15.11
RX/SCL8: J49.4, J50.4, J52.TXO, J53.4, R34.1, U17.11
RX/SCL9: J55.4, J56.4, J58.TXO, J59.4, R38.1, U19.11
RX/SCL10: J61.4, J62.4, J64.TXO, J65.4, R42.1, U21.11
RX/SCL11: J67.4, J68.4, J70.TXO, J71.4, R46.1, U23.11
RX/SCL12: J73.4, J74.4, J76.TXO, J77.4, R50.1, U25.11
RX/SCL13: J79.4, J80.4, J82.TXO, J83.4, R54.1, U27.11
RX/SCL14: J85.4, J86.4, J88.TXO, J89.4, R58.1, U29.11
RX/SCL15: J91.4, J92.4, J94.TXO, J95.4, R62.1, U31.11
RX/SCL16: J97.4, J98.4, J100.TXO, J101.4, R66.1, U33.11
RX/SCL17: J103.4, J104.4, J106.TXO, J107.4, R70.1, U35.11
RX/SCL18: J109.4, J110.4, J112.TXO, J113.4, R74.1, U37.11
RX/SCL19: J115.4, J116.4, J118.TXO, J119.4, R78.1, U39.11
RX/SCL20: J121.4, J122.4, J124.TXO, J125.4, R82.1, U41.11
RX/SCL21: J127.4, J128.4, J130.TXO, J131.4, R86.1, U43.11
RX/SCL22: J133.4, J134.4, J136.TXO, J137.4, R90.1, U45.11
RX/SCL23: J139.4, J140.4, J142.TXO, J143.4, R94.1, U47.11
RX/SCL24: J145.4, J146.4, J148.TXO, J149.4, R98.1, U49.11
RX/SCL25: J151.4, J152.4, J154.TXO, J155.4, R102.1, U51.11
RX/SCL26: J157.4, J158.4, J160.TXO, J161.4, R106.1, U53.11
RX/SCL27: J163.4, J164.4, J166.TXO, J167.4, R110.1, U55.11
RX/SCL28: J169.4, J170.4, J172.TXO, J173.4, R114.1, U57.11
RX/SCL29: J175.4, J176.4, J178.TXO, J179.4, R118.1, U59.11
RX/SCL30: J181.4, J182.4, J184.TXO, J185.4, R122.1, U61.11
RX/SCL31: J187.4, J188.4, J190.TXO, J191.4, R126.1, U63.11
RX/SCL32: J193.4, J194.4, J196.TXO, J197.4, R130.1, U65.11
RX/SCL33: J199.4, J200.4, J202.TXO, J203.4, R134.1, U67.11
RX/SCL34: J205.4, J206.4, J208.TXO, J209.4, R138.1, U69.11
RX/SCL35: J211.4, J212.4, J214.TXO, J215.4, R142.1, U71.11
RX/SCL36: J217.4, J218.4, J220.TXO, J221.4, R146.1, U73.11
RX/SCL37: J223.4, J224.4, J226.TXO, J227.4, R150.1, U75.11
RX/SCL38: J229.4, J230.4, J232.TXO, J233.4, R154.1, U77.11
RX/SCL39: J235.4, J236.4, J238.TXO, J239.4, R158.1, U79.11
SCK: J5.3, U1.3, U3.6
SCK1: J12.3, U2.3, U4.6
SCK2: J18.3, U5.3, U6.6
SCK3: J24.3, U7.3, U8.6
SCK4: J30.3, U9.3, U10.6
SCK5: J36.3, U11.3, U12.6
SCK6: J42.3, U13.3, U14.6
SCK7: J48.3, U15.3, U16.6
SCK8: J54.3, U17.3, U18.6
SCK9: J60.3, U19.3, U20.6
SCK10: J66.3, U21.3, U22.6
SCK11: J72.3, U23.3, U24.6
SCK12: J78.3, U25.3, U26.6
SCK13: J84.3, U27.3, U28.6
SCK14: J90.3, U29.3, U30.6
SCK15: J96.3, U31.3, U32.6
SCK16: J102.3, U33.3, U34.6
SCK17: J108.3, U35.3, U36.6
SCK18: J114.3, U37.3, U38.6
SCK19: J120.3, U39.3, U40.6
SCK20: J126.3, U41.3, U42.6
SCK21: J132.3, U43.3, U44.6
SCK22: J138.3, U45.3, U46.6
SCK23: J144.3, U47.3, U48.6
SCK24: J150.3, U49.3, U50.6
SCK25: J156.3, U51.3, U52.6
SCK26: J162.3, U53.3, U54.6
SCK27: J168.3, U55.3, U56.6
SCK28: J174.3, U57.3, U58.6
SCK29: J180.3, U59.3, U60.6
SCK30: J186.3, U61.3, U62.6
SCK31: J192.3, U63.3, U64.6
SCK32: J198.3, U65.3, U66.6
SCK33: J204.3, U67.3, U68.6
SCK34: J210.3, U69.3, U70.6
SCK35: J216.3, U71.3, U72.6
SCK36: J222.3, U73.3, U74.6
SCK37: J228.3, U75.3, U76.6
SCK38: J234.3, U77.3, U78.6
SCK39: J240.3, U79.3, U80.6
TX/SDA: J1.3, J2.RXI, J4.3, J8.3, R13.1, U1.12
TX/SDA1: J6.3, J7.3, J10.RXI, J11.3, R1.1, U2.12
TX/SDA2: J13.3, J14.3, J16.RXI, J17.3, R7.1, U5.12
TX/SDA3: J19.3, J20.3, J22.RXI, J23.3, R11.1, U7.12
TX/SDA4: J25.3, J26.3, J28.RXI, J29.3, R17.1, U9.12
TX/SDA5: J31.3, J32.3, J34.RXI, J35.3, R21.1, U11.12
TX/SDA6: J37.3, J38.3, J40.RXI, J41.3, R25.1, U13.12
TX/SDA7: J43.3, J44.3, J46.RXI, J47.3, R29.1, U15.12
TX/SDA8: J49.3, J50.3, J52.RXI, J53.3, R33.1, U17.12
TX/SDA9: J55.3, J56.3, J58.RXI, J59.3, R37.1, U19.12
TX/SDA10: J61.3, J62.3, J64.RXI, J65.3, R41.1, U21.12
TX/SDA11: J67.3, J68.3, J70.RXI, J71.3, R45.1, U23.12
TX/SDA12: J73.3, J74.3, J76.RXI, J77.3, R49.1, U25.12
TX/SDA13: J79.3, J80.3, J82.RXI, J83.3, R53.1, U27.12
TX/SDA14: J85.3, J86.3, J88.RXI, J89.3, R57.1, U29.12
TX/SDA15: J91.3, J92.3, J94.RXI, J95.3, R61.1, U31.12
TX/SDA16: J97.3, J98.3, J100.RXI, J101.3, R65.1, U33.12
TX/SDA17: J103.3, J104.3, J106.RXI, J107.3, R69.1, U35.12
TX/SDA18: J109.3, J110.3, J112.RXI, J113.3, R73.1, U37.12
TX/SDA19: J115.3, J116.3, J118.RXI, J119.3, R77.1, U39.12
TX/SDA20: J121.3, J122.3, J124.RXI, J125.3, R81.1, U41.12
TX/SDA21: J127.3, J128.3, J130.RXI, J131.3, R85.1, U43.12
TX/SDA22: J133.3, J134.3, J136.RXI, J137.3, R89.1, U45.12
TX/SDA23: J139.3, J140.3, J142.RXI, J143.3, R93.1, U47.12
TX/SDA24: J145.3, J146.3, J148.RXI, J149.3, R97.1, U49.12
TX/SDA25: J151.3, J152.3, J154.RXI, J155.3, R101.1, U51.12
TX/SDA26: J157.3, J158.3, J160.RXI, J161.3, R105.1, U53.12
TX/SDA27: J163.3, J164.3, J166.RXI, J167.3, R109.1, U55.12
TX/SDA28: J169.3, J170.3, J172.RXI, J173.3, R113.1, U57.12
TX/SDA29: J175.3, J176.3, J178.RXI, J179.3, R117.1, U59.12
TX/SDA30: J181.3, J182.3, J184.RXI, J185.3, R121.1, U61.12
TX/SDA31: J187.3, J188.3, J190.RXI, J191.3, R125.1, U63.12
TX/SDA32: J193.3, J194.3, J196.RXI, J197.3, R129.1, U65.12
TX/SDA33: J199.3, J200.3, J202.RXI, J203.3, R133.1, U67.12
TX/SDA34: J205.3, J206.3, J208.RXI, J209.3, R137.1, U69.12
TX/SDA35: J211.3, J212.3, J214.RXI, J215.3, R141.1, U71.12
TX/SDA36: J217.3, J218.3, J220.RXI, J221.3, R145.1, U73.12
TX/SDA37: J223.3, J224.3, J226.RXI, J227.3, R149.1, U75.12
TX/SDA38: J229.3, J230.3, J232.RXI, J233.3, R153.1, U77.12
TX/SDA39: J235.3, J236.3, J238.RXI, J239.3, R157.1, U79.12

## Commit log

2017-06-19 Added readme, .gitignore, etc...
2017-06-19 Formatted repo
2017-06-19 Updated LED
2017-06-19 Added LED, I2C connectors to SFE library and changed components in schematic
2017-06-20 Updated all schematics to point to proper library
2017-06-26 Fixed minor borad layout issues
2017-06-27 Post design review changes. Cream on JP1 and AS726X still needs to be changed
2017-06-27 Added .stl for enclosure
2017-06-28 Made final changes to tCream on AS726X
2017-06-28 Continued to update with checklist
2017-06-28 Misc. changes, post design review
2017-07-03 Final changes before 2nd Design Review
2017-07-05 Final post design review changes
2017-07-06 Changed version number to match SFE style
2017-07-06 Added Firmware
2017-07-06 Moved enclosure
2017-07-06 Added .stl of programmer
2017-07-10 Started work on library, still untested
2017-07-11 Library Functions, must add Wire selection
2017-07-12 Added non default constructor, License in wrong place
2017-07-19 Added label to JP4
2017-07-21 Changed version number
2017-07-24 Squashed 'Libraries/Arduino/' content from commit c1fc430
    git-subtree-dir: Libraries/Arduino
    git-subtree-split: c1fc4301b125d5a296ba35155b57e9aedd8828c4
2017-07-24 Removed old library structure
2017-07-24 Updated Readme again
2017-07-24 Yet some more README fixes
2017-07-25 Changed board version
2017-07-25 Fixed qwiic conn
2017-08-10 panel
2017-08-15 changed dimensions
2017-08-23 Moved engineering checklist
2017-09-12 Cleaned library and repo
2017-09-12 Squashed 'Libraries/Arduino/' content from commit fdb7230
    git-subtree-dir: Libraries/Arduino
    git-subtree-split: fdb7230b3d93a20c6f5643e600e2dbba81a91f10
2017-09-12 More cleaning
2017-09-20 Added Photo
2017-10-19 Updating readme
2017-10-19 Squashed 'Libraries/Arduino/' content from commit edc2b6d
    git-subtree-dir: Libraries/Arduino
    git-subtree-split: edc2b6d7eaa1af2b5196feef1b4779a1a61ffca9
2018-04-16 Triple jumper Aperture blowout
2020-03-12 Update README.md
    Link to correct code repo
2020-03-12 Update README.md
    Update description
2020-03-12 Remove Outdated Library and Point to Repo for Arduino Library
    Remove outdated library and remove redundancy by pointing to the repository for the Arduino library.
2023-10-03 Remove back ZIP file
    Fix for issue #7
